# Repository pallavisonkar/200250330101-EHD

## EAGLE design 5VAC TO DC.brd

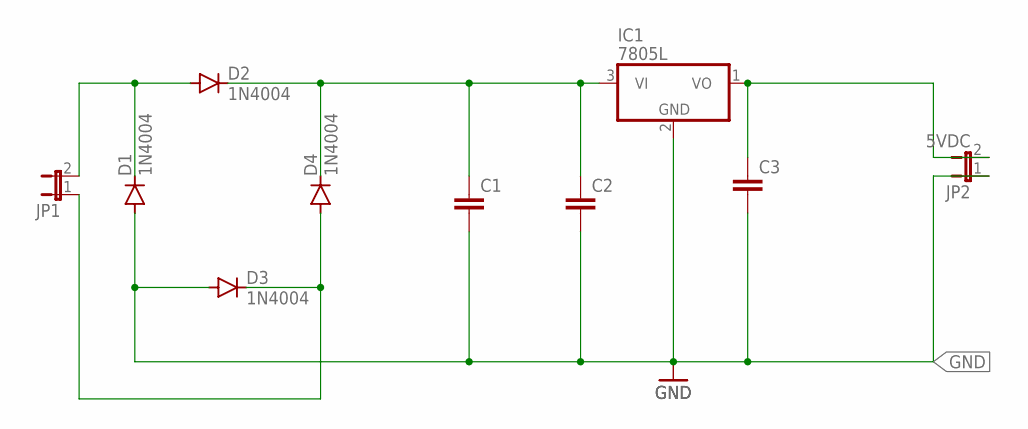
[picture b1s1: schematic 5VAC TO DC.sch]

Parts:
C1, C2, C3: C2,5-3; C2.5-3
D1, D2, D3, D4: 1N4004; DO41-10
IC1: 7805L; TO92
JP1: JP1E; JP1
JP2: 5VDC; JP1

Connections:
GND: C1.2, C2.2, C3.2, D1.A, D3.A, IC1.2 (GND), JP2.1
unnamed: D1.C, D2.A, JP1.2
unnamed: C1.1, C2.1, D2.C, D4.C, IC1.3 (VI)
unnamed: C3.1, IC1.1 (VO), JP2.2
unnamed: D3.C, D4.A, JP1.1

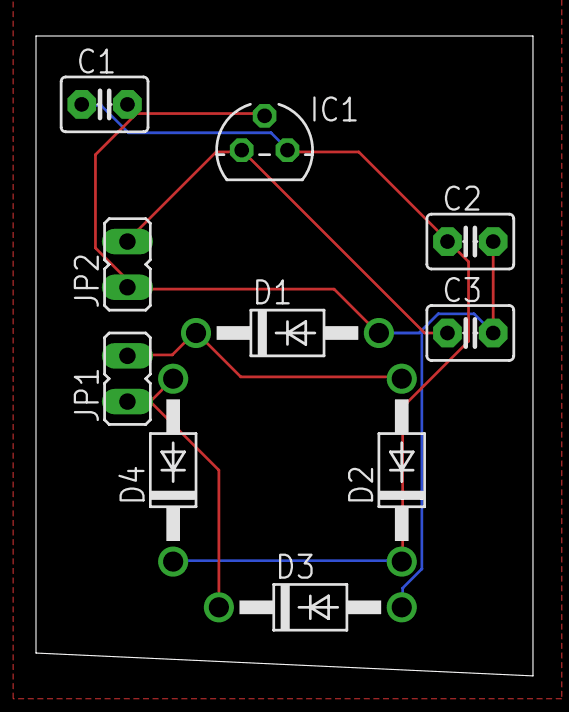
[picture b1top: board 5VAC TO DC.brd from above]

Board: 2 copper layers, 27.6 x 35.6 mm, 10 parts (0 on the bottom side), 5 nets.
